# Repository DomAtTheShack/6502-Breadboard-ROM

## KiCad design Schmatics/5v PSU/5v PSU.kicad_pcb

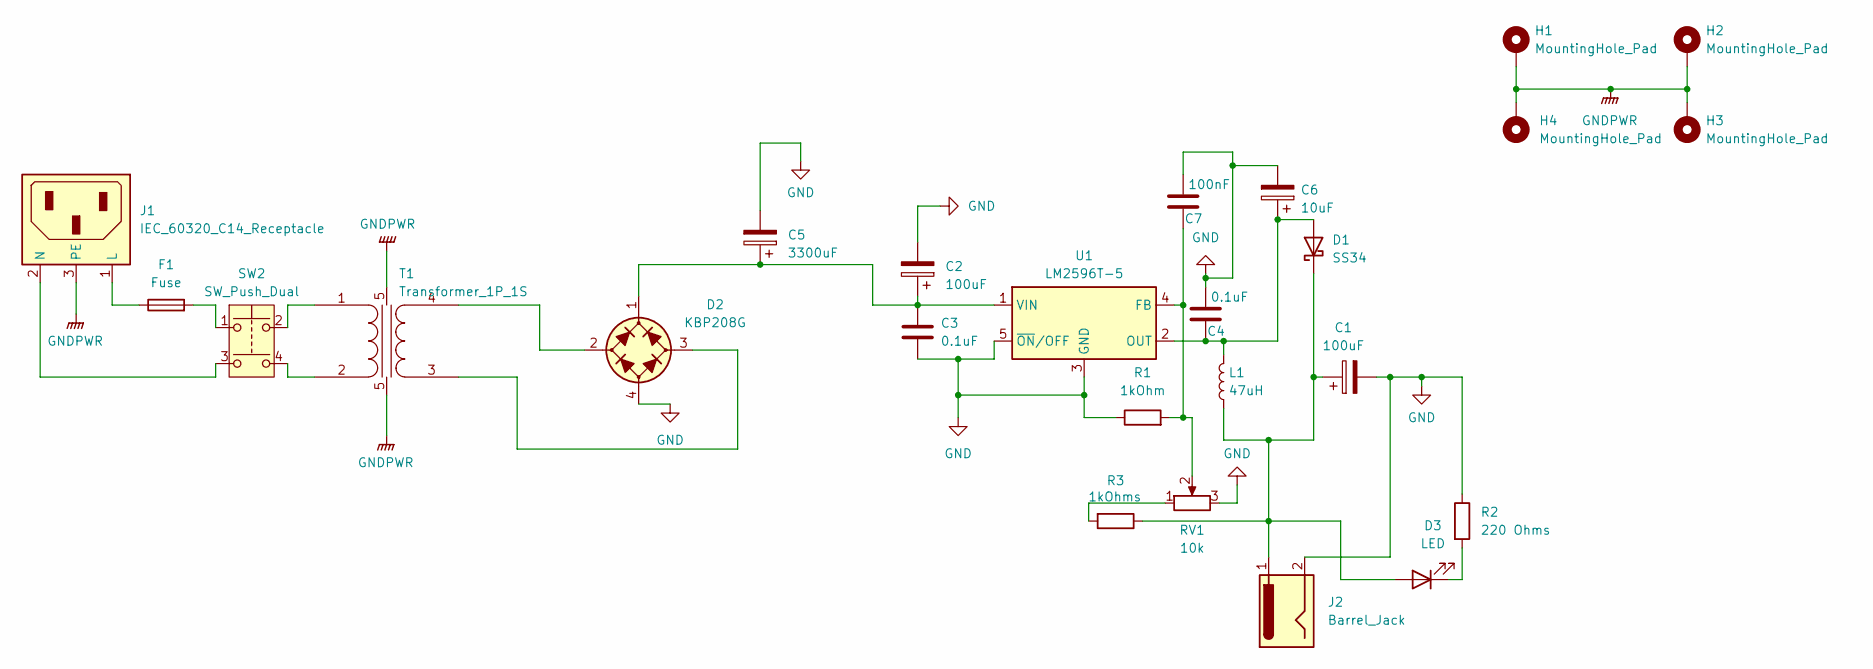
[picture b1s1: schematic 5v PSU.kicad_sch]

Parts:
C1, C2: 100uF; CP_Radial_D5.0mm_P2.00mm
C3, C4: 0.1uF; C_Axial_L3.8mm_D2.6mm_P7.50mm_Horizontal
C5: 3300uF; CP_Radial_D16.0mm_P7.50mm
C6: 10uF; CP_Radial_D5.0mm_P2.00mm
C7: 100nF; C_Axial_L3.8mm_D2.6mm_P7.50mm_Horizontal
D1: SS34; D_5W_P10.16mm_Horizontal
D2: KBP208G; Diode_Bridge_KBP
D3: LED; LED_D2.0mm_W4.8mm_H2.5mm_FlatTop
F1: Fuse; Fuseholder_Clip-6.3x32mm_Littelfuse_102071_Inline_P34.70x7.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
H1, H2, H3, H4: MountingHole_Pad; MountingHole_2.2mm_M2_DIN965_Pad
J1: IEC_60320_C14_Receptacle; IEC_THT
J2: Barrel_Jack; BarrelJack_SwitchcraftConxall_RAPC10U_Horizontal
L1: 47uH; L_Axial_L5.3mm_D2.2mm_P10.16mm_Horizontal_Vishay_IM-1
R1: 1kOhm; R_Axial_DIN0207_L6.3mm_D2.5mm_P10.16mm_Horizontal
R2: 220 Ohms; R_Axial_DIN0207_L6.3mm_D2.5mm_P10.16mm_Horizontal
R3: 1kOhms; R_Axial_DIN0207_L6.3mm_D2.5mm_P10.16mm_Horizontal
RV1: 10k; Potentiometer_Alps_RK09L_Single_Vertical
SW2: SW_Push_Dual; ST24_SWITCH
T1: Transformer_1P_1S; Transformer_166J
U1: LM2596T-5; TO-220-5_P3.4x3.7mm_StaggerOdd_Lead3.8mm_Vertical

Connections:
GND: C1.2, C2.2, C3.2, C4.1, C5.2, C6.2, C7.1, D2.4 (-), J2.2, R1.1, R2.1, RV1.3, U1.3 (GND), U1.5 (~ON/OFF)
GNDPWR: H1.1, H2.1, H3.1, H4.1, J1.3 (PE), T1.5 (EGND)
unnamed: C4.2, C6.1, D1.2 (A), L1.2, U1.2 (OUT)
unnamed: C1.1, D1.1 (K), D3.2 (A), J2.1, L1.1, R3.1
unnamed: D2.2 (1), T1.4 (SB)
unnamed: D2.3 (2), T1.3 (SA)
unnamed: C2.1, C3.1, C5.1, D2.1 (+), U1.1 (VIN)
unnamed: D3.1 (K), R2.2
unnamed: F1.2, SW2.1
unnamed: F1.1, J1.1 (L)
unnamed: J1.2 (N), SW2.3
unnamed: R3.2, RV1.1
unnamed: SW2.2, T1.1 (AA)
unnamed: SW2.4, T1.2 (AB)
unnamed: C7.2, R1.2, RV1.2, U1.4 (FB)

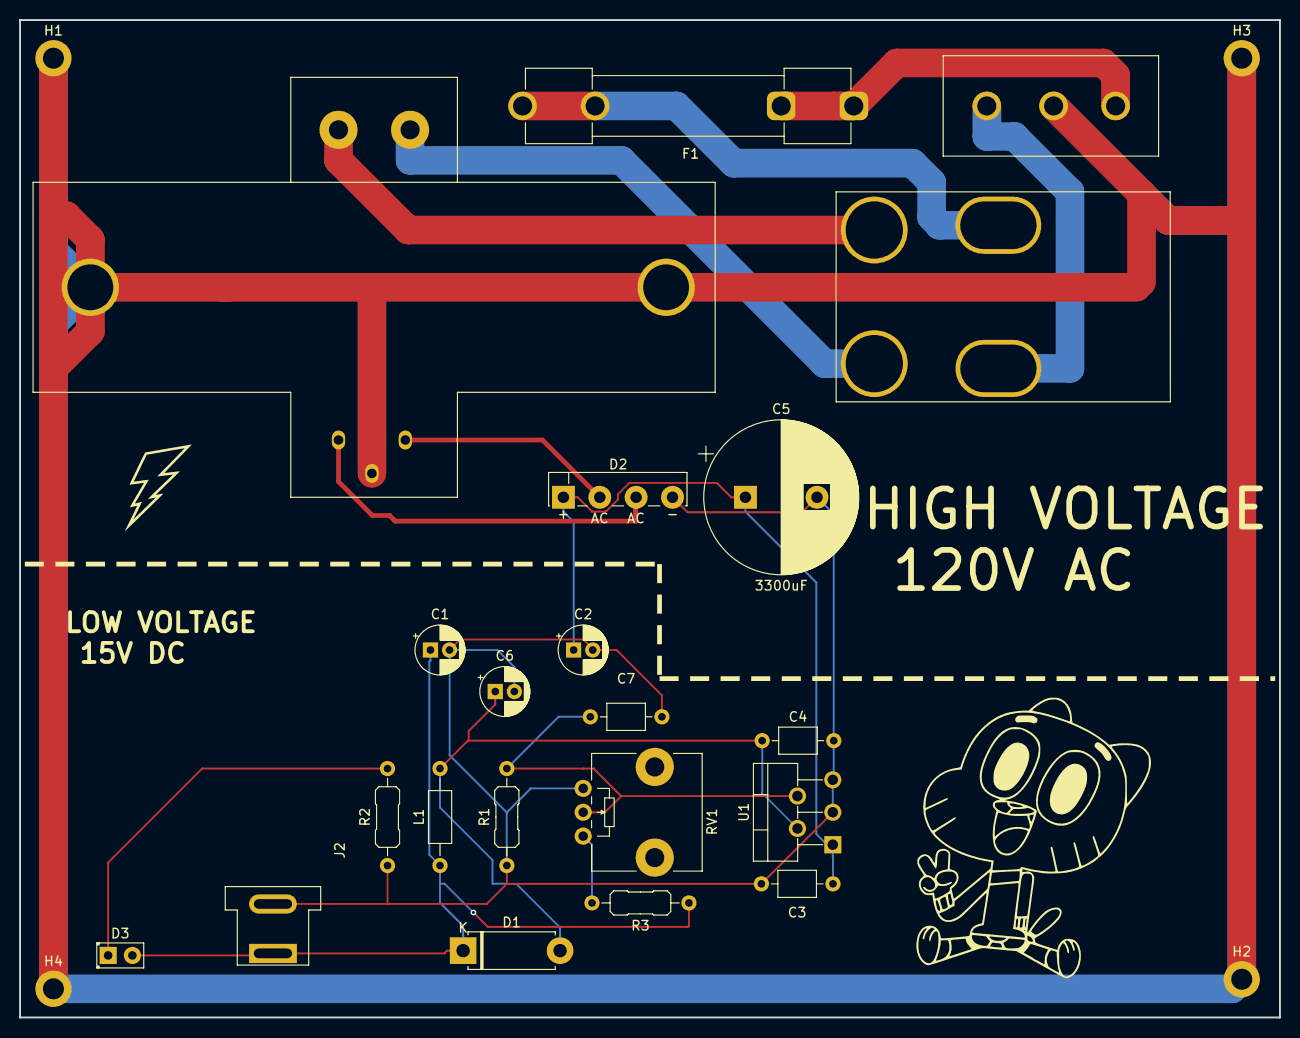
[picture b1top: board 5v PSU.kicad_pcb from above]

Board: 2 copper layers, 132.0 x 104.5 mm, 27 parts (0 on the bottom side), 15 nets.

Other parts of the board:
G1, G2: LOGO

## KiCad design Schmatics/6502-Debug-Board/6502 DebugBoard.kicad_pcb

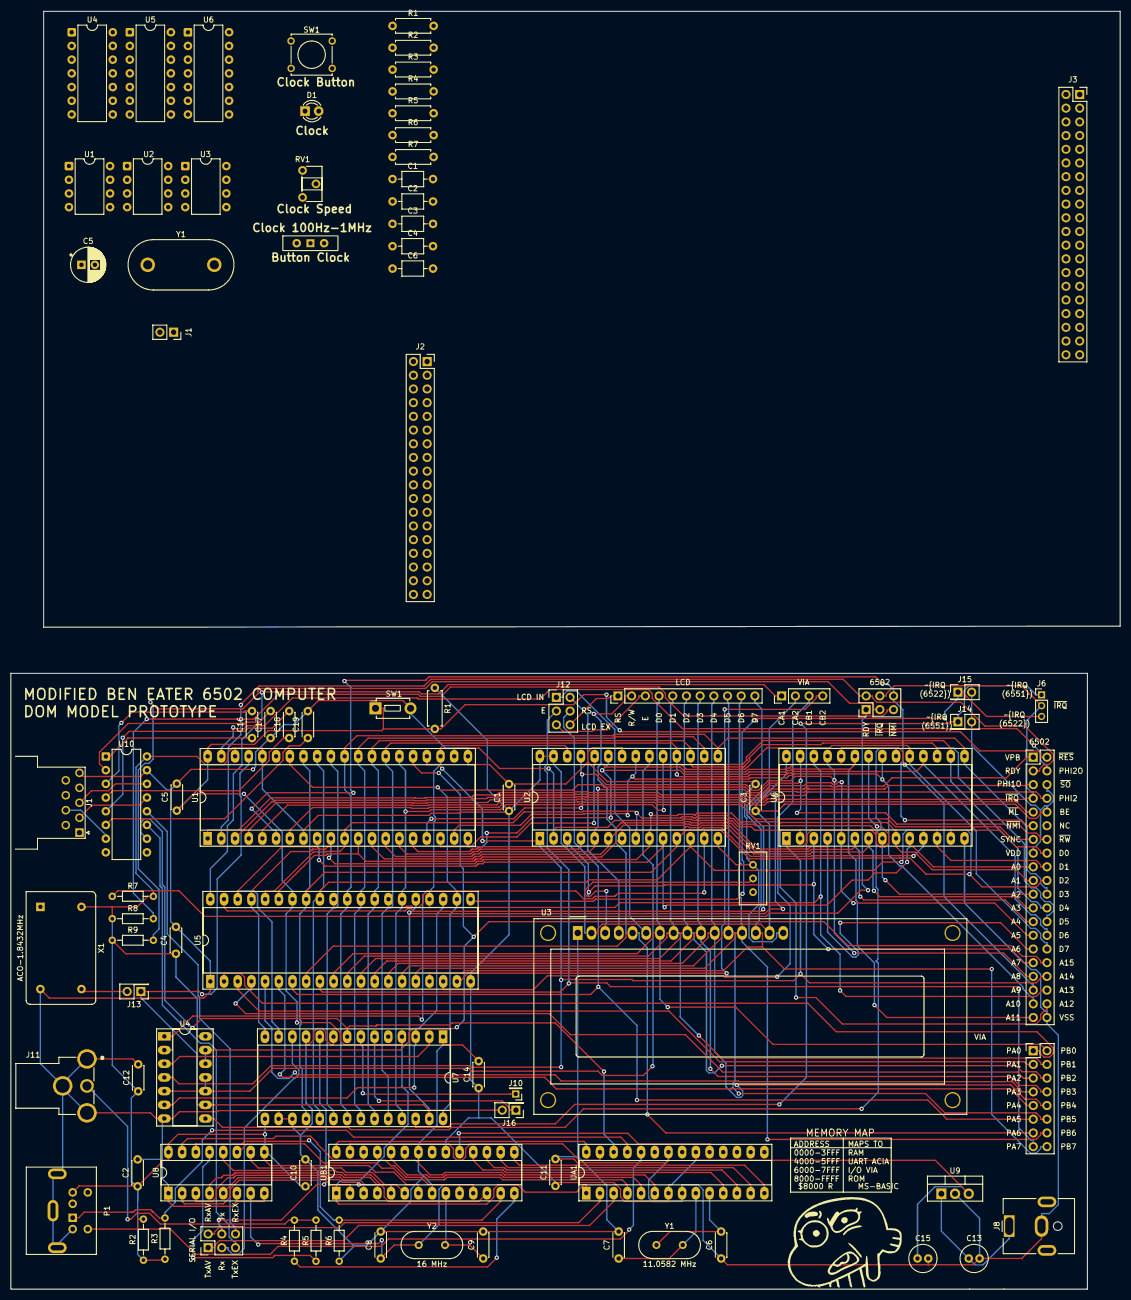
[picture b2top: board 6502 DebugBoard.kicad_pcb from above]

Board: 2 copper layers, 205.6 x 236.8 mm, 89 parts (0 on the bottom side), 141 nets.

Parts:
C1, C2#2, C3, C4, C10, C11, C12, C14: 0.1uF; C_Disc_D4.3mm_W1.9mm_P5.00mm
C1#2: 22pf; C_Axial_L3.8mm_D2.6mm_P7.50mm_Horizontal
C2: 100nf; C_Axial_L3.8mm_D2.6mm_P7.50mm_Horizontal
C3#2, C4#2, C6#2: 10nf; C_Axial_L3.8mm_D2.6mm_P7.50mm_Horizontal
C5: 47uf; CP_Radial_D6.3mm_P2.50mm
C5#2: 0.1; C_Disc_D4.3mm_W1.9mm_P5.00mm
C6, C7, C8, C9: 22pF; C_Disc_D4.3mm_W1.9mm_P5.00mm
C13, C15: 10uf; C_Radial_D5.0mm_H11.0mm_P2.00mm
C16, C17, C18, C19: 1uf; C_Disc_D4.3mm_W1.9mm_P5.00mm
D1: LED; LED_D3.0mm
J1: Conn_01x02; PinSocket_1x02_P2.54mm_Vertical
J1#2: DE9_Pins; DSUB-9_Socket_Horizontal_P2.77x2.54mm_EdgePinOffset9.40mm
J2: Conn_02x20_Odd_Even; PinHeader_2x20_P2.54mm_Vertical
J2#2: Conn_02x18_Top_Bottom; PinSocket_2x18_P2.54mm_Vertical
J3: Conn_01x04_Male; PinHeader_1x04_P2.54mm_Vertical
J3#2: Conn_02x20_Top_Bottom; PinSocket_2x20_P2.54mm_Vertical
J4, J7, J12: Conn_02x03_Odd_Even; PinHeader_2x03_P2.54mm_Vertical
J5: Conn_02x08_Odd_Even; PinHeader_2x08_P2.54mm_Vertical
J6: Conn_01x03; PinHeader_1x03_P2.00mm_Vertical
J8: Barrel_Jack; BarrelJack_CUI_PJ-063AH_Horizontal
J9: Conn_01x11_Male; PinHeader_1x11_P2.54mm_Vertical
J10: Conn_01x01; PinHeader_1x01_P2.00mm_Vertical
J11: RCJ-017; CUI_RCJ-017
J13, J14, J15, J16: Conn_02x01; PinHeader_2x01_P2.54mm_Vertical
P1: Mini-DIN_6pins; Connector_Mini-DIN_Female_6Pin_2rows
R1: 1K; R_Axial_DIN0207_L6.3mm_D2.5mm_P7.62mm_Horizontal
R1#2: 1M; R_Axial_DIN0207_L6.3mm_D2.5mm_P7.62mm_Horizontal
R2, R3, R6, R7#2, R8, R9: 10k; R_Axial_DIN0204_L3.6mm_D1.6mm_P7.62mm_Horizontal
R2#2, R5, R6#2, R7: 1k; R_Axial_DIN0207_L6.3mm_D2.5mm_P7.62mm_Horizontal
R3#2: 6.9k; R_Axial_DIN0207_L6.3mm_D2.5mm_P7.62mm_Horizontal
R4: 1k; R_Axial_DIN0204_L3.6mm_D1.6mm_P7.62mm_Horizontal
R4#2: 10k; R_Axial_DIN0207_L6.3mm_D2.5mm_P7.62mm_Horizontal
R5#2: 470 Ohms; R_Axial_DIN0204_L3.6mm_D1.6mm_P7.62mm_Horizontal
RV1: R_Potentiometer; Potentiometer_ACP_CA6-H2,5_Horizontal
RV1#2: R_POT_TRIM_US; Potentiometer_Bourns_3386C_Horizontal
SW1: SW_Push; SW_Tactile_Straight_KSA0Axx1LFTR
SW1#2: RESET; SW_PUSH_1P1T_6x3.5mm_H4.3_APEM_MJTP1243
SW2: SW_Nidec_CAS-120A1; SW_Slide-03_Wuerth-WS-SLTV_10x2.5x6.4_P2.54mm
U1: WD65C02; DIP-40_W15.24mm_Socket_LongPads
U1#2, U2, U3#2: LM555xN; DIP-8_W7.62mm
U2#2: 28C256; DIP-28_W15.24mm_Socket_LongPads
U3: WC1602A
U4: 74HC00; DIP-14_W7.62mm_Socket_LongPads
U4#2: 74LS04; DIP-14_W7.62mm
U5: 74LS08; DIP-14_W7.62mm
U5#2: WD65C22; DIP-40_W15.24mm_Socket_LongPads
U6: CY62256-70PC; DIP-28_W15.24mm_Socket_LongPads
U6#2: 74LS32; DIP-14_W7.62mm
U7: 6551; DIP-28_W15.24mm_Socket_LongPads
U8: 74HC166; DIP-16_W7.62mm_Socket_LongPads
U9: LM7805_TO220; TO-220-3_Vertical
U10: MAX232; DIP-16_W7.62mm
UA1: ATmega328P-PU; DIP-28_W7.62mm_Socket_LongPads
UB1: ATmega328P-PU; DIP-28_W7.62mm_Socket_LongPads
X1: ACO-1.8432MHz; Oscillator_DIP-14
Y1: 11.0582 MHz; Crystal_HC49-4H_Vertical
Y1#2: Crystal; Crystal_HC33-U_Vertical
Y2: 16 MHz; Crystal_HC49-4H_Vertical

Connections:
+5V: C1.1, C2#2.1, C3.1, C4.1, C10.1, C11.1, C12.1, C14.1, C15.1, J2.6, J2.10, J2.15, J2#2.1, J2#2.19, J14.2, J15.2, P1.4, R1.1, R2.1, R2#2.2, R3.1, R3#2.2, R4#2.2, R5.1, R7.1, R7#2.2, R8.1, R9.1, U1.8 (VCC), U1.36 (BE), U1.38 (~SO), U1#2.4 (R), U1#2.8 (VCC), U2.4 (R), U2.8 (VCC), U2#2.27 (~WE), U2#2.28 (VCC), U3.2 (VDD), U3.15 (LED(+)), U3#2.8 (VCC), U4.14 (VCC), U4#2.14 (VCC), U5.14 (VCC), U5#2.20 (VCC), U6.28 (VCC), U6#2.14 (VCC), U7.15 (VCC), U8.9 (~CLR), U8.16 (VCC), U9.3 (VO), U10.16 (VCC), UA1.7 (VCC), UA1.20 (AVCC), UB1.7 (VCC), UB1.20 (AVCC), X1.14 (Vcc)
GND: C1.2, C1#2.1, C2.1, C2#2.2, C3.2, C3#2.2, C4.2, C4#2.2, C5.2, C5#2.2, C6.1, C6#2.1, C7.2, C8.2, C9.2, C10.2, C11.2, C12.2, C13.2, C14.2, C15.2, C17.1, C19.2, J1#2.5, J2.40, J2#2.18, J2#2.36, J8.2, J11.1A, J11.1B, J11.1C, P1.3, P1.7 (Shell), R6.1, RV1#2.1, SW1.2, SW1#2.2, SW2.2 (B), U1.21 (GND), U1#2.1 (GND), U2.1 (GND), U2#2.14 (GND), U2#2.22 (~OE), U3.1 (VSS), U3.16 (LED(-)), U3#2.1 (GND), U3#2.6 (THR), U4.7 (GND), U4#2.7 (GND), U5.7 (GND), U5#2.1 (GND), U6.14 (GND), U6#2.7 (GND), U7.1 (GND), U7.9 (~CTS), U7.11 (~DTR), U7.16 (~DCD), U7.17 (~DSR), U8.1 (SER), U8.6 (CLK_INH), U8.8 (GND), U9.2 (GND), U10.15 (GND), UA1.8 (GND), UA1.22 (GND), UB1.8 (GND), UB1.22 (GND), X1.7 (GND)
unnamed: D1.2 (A), U6#2.3
unnamed: D1.1 (K), R7.2
unnamed: C1#2.2, J1.1, R1#2.2, Y1#2.2
unnamed: J1.2, R1#2.1, Y1#2.1
unnamed: J2.1, U1.1 (~VP)
unnamed: C5#2.1, J2.2, R1.2, SW1#2.1, U1.40 (~RESET), U5#2.34 (~RESET), U7.4 (~RESET), UA1.1 (~RESET/PC6), UB1.1 (~RESET/PC6)
unnamed: J2.3, J7.2, U1.2 (RDY)
unnamed: J2.4, U1.39 (PHI2out)
unnamed: J2.5, U1.3 (PHI1out)
unnamed: J2.7, J6.2, J7.4, U1.4 (~IRQ)
unnamed: J2.9, U1.5 (~ML)
unnamed: J2.11, J7.6, U1.6 (~NMI)
unnamed: J2.13, U1.7 (SYNC)
unnamed: J2.14, U1.34 (R/~W), U5#2.22 (R/~W), U6.27 (~WE), U7.28 (R/~W)
unnamed: J2.16, U1.33 (D0), U2#2.11 (D0), U5#2.33 (D0), U6.11 (Q0), U7.18 (D0)
unnamed: J2.17, U1.9 (A0), U2#2.10 (A0), U5#2.38 (RS0), U6.10 (A0), U7.13 (RS0)
unnamed: J2.18, U1.32 (D1), U2#2.12 (D1), U5#2.32 (D1), U6.12 (Q1), U7.19 (D1)
unnamed: J2.19, U1.10 (A1), U2#2.9 (A1), U5#2.37 (RS1), U6.9 (A1), U7.14 (RS1)
unnamed: J2.20, U1.31 (D2), U2#2.13 (D2), U5#2.31 (D2), U6.13 (Q2), U7.20 (D2)
unnamed: J2.21, U1.11 (A2), U2#2.8 (A2), U5#2.36 (RS2), U6.8 (A2)
unnamed: J2.22, U1.30 (D3), U2#2.15 (D3), U5#2.30 (D3), U6.15 (Q3), U7.21 (D3)
unnamed: J2.23, U1.12 (A3), U2#2.7 (A3), U5#2.35 (RS3), U6.7 (A3)
unnamed: J2.24, U1.29 (D4), U2#2.16 (D4), U5#2.29 (D4), U6.16 (Q4), U7.22 (D4)
unnamed: J2.25, U1.13 (A4), U2#2.6 (A4), U6.6 (A4)
unnamed: J2.26, U1.28 (D5), U2#2.17 (D5), U5#2.28 (D5), U6.17 (Q5), U7.23 (D5)
unnamed: J2.27, U1.14 (A5), U2#2.5 (A5), U6.5 (A5)
unnamed: J2.28, U1.27 (D6), U2#2.18 (D6), U5#2.27 (D6), U6.18 (Q6), U7.24 (D6)
unnamed: J2.29, U1.15 (A6), U2#2.4 (A6), U6.4 (A6)
unnamed: J2.30, U1.26 (D7), U2#2.19 (D7), U5#2.26 (D7), U6.19 (Q7), U7.25 (D7)
unnamed: J2.31, U1.16 (A7), U2#2.3 (A7), U6.3 (A7)
unnamed: J2.32, U1.25 (A15), U4.12, U4.13
unnamed: J2.33, U1.17 (A8), U2#2.25 (A8), U6.25 (A8)
unnamed: J2.34, U1.24 (A14), U2#2.1 (A14), U4.4, U6.1 (A14), U6.22 (~OE)
unnamed: J2.35, U1.18 (A9), U2#2.24 (A9), U6.24 (A9)
unnamed: J2.36, U1.23 (A13), U2#2.26 (A13), U4.1, U4.2, U5#2.24 (CS1), U6.26 (A13)
unnamed: J2.37, U1.19 (A10), U2#2.21 (A10), U6.21 (A10)
unnamed: J2.38, U1.22 (A12), U2#2.2 (A12), U6.2 (A12)
unnamed: J2.39, U1.20 (A11), U2#2.23 (A11), U6.23 (A11)
unnamed: J3.1, U5#2.40 (CA1)
unnamed: J3.2, U5#2.39 (CA2)
unnamed: J3.3, U5#2.18 (CB1)
unnamed: J3.4, U5#2.19 (CB2)
unnamed: J3#2.20, J3#2.40
unnamed: J4.1, UA1.3 (PD1)
unnamed: J4.2, UA1.2 (PD0)
unnamed: J4.3, U7.12 (Rx_Data)
unnamed: J4.4, U7.10 (Tx_Data)
unnamed: J4.5, U10.11 (T1IN)
unnamed: J4.6, U10.12 (R1OUT)
unnamed: J5.1, U5#2.2 (PA0)
unnamed: J5.2, J9.4, U3.7 (D0), U5#2.10 (PB0)
unnamed: J5.3, U5#2.3 (PA1)
unnamed: J5.4, J9.5, U3.8 (D1), U5#2.11 (PB1)
unnamed: J5.5, U5#2.4 (PA2)
unnamed: J5.6, J9.6, U3.9 (D2), U5#2.12 (PB2)
unnamed: J5.7, U5#2.5 (PA3)
unnamed: J5.8, J9.7, U3.10 (D3), U5#2.13 (PB3)
unnamed: J5.9, U5#2.6 (PA4)
unnamed: J5.10, J9.8, U3.11 (D4), U5#2.14 (PB4)
unnamed: J5.12, J9.9, U3.12 (D5), U5#2.15 (PB5)
unnamed: J5.13, J9.2, U3.5 (R/W), U5#2.8 (PA6)
unnamed: J5.14, J9.10, U3.13 (D6), U5#2.16 (PB6)
unnamed: J5.16, J9.11, U3.14 (D7), U5#2.17 (PB7)
unnamed: J7.1, R7#2.1
unnamed: J7.3, R9.2
unnamed: J7.5, R8.2
unnamed: J10.1, U7.7 (XLT0)
unnamed: J11.1 (V_In), R4.2, R5#2.2
unnamed: J12.1, U3.6 (E)
unnamed: J12.2, U3.4 (RS)
unnamed: J5.15, J12.3, U5#2.9 (PA7)
unnamed: J5.11, J12.4, U5#2.7 (PA5)
unnamed: J9.3, J12.5
unnamed: J9.1, J12.6
unnamed: J2.8, J13.1, J16.2, U1.37 (PHI2), U4.9, U5#2.25 (PHI2), U7.27 (PHI2)
unnamed: J13.2, X1.8 (OUT)
unnamed: J6.1, J14.1, U7.26 (~IRQ)
unnamed: J6.3, J15.1, U5#2.21 (~IRQ)
unnamed: J16.1, U7.6 (XTLI)
unnamed: R3#2.1, RV1.1
unnamed: R5.2, SW2.3 (A), U3#2.4 (R)
unnamed: R6#2.1, SW2.1 (C)
unnamed: C3#2.1, U1#2.5 (CV)
unnamed: R2#2.1, U1#2.7 (DIS)
unnamed: U1#2.3 (Q), U5.4
unnamed: C2.2, RV1.2, U1#2.2 (TR), U1#2.6 (THR)
unnamed: C4#2.1, U2.5 (CV)
unnamed: C5.1, U2.6 (THR), U2.7 (DIS)
unnamed: U2.3 (Q), U5.1
unnamed: R4#2.1, SW1.1, U2.2 (TR)
unnamed: U2#2.20 (~CS), U4.5, U4.10, U4.11
unnamed: C6#2.2, U3#2.5 (CV)
unnamed: U3#2.3 (Q), U4#2.1, U5.5
unnamed: R6#2.2, U3#2.2 (TR)
unnamed: RV1#2.2, U3.3 (VO)
unnamed: U4#2.2, U5.2
unnamed: U5.3, U6#2.1
unnamed: U5.6, U6#2.2
unnamed: U4.6, U5#2.23 (~CS2), U7.3 (~CS1)
unnamed: U4.8, U6.20 (~CS)
unnamed: U4.3, U7.2 (CS0)
unnamed: U8.2 (A), UB1.2 (PD0)
unnamed: U8.3 (B), UB1.3 (PD1)
unnamed: U8.4 (C), UB1.4 (PD2)
unnamed: C8.1, U8.7 (CLK), UB1.10 (XTAL2/PB7), Y2.1
unnamed: U8.5 (D), UB1.5 (PD3)
unnamed: U8.10 (E), UB1.6 (PD4)
unnamed: U8.11 (F), UB1.11 (PD5)
unnamed: U8.12 (G), UB1.12 (PD6)
unnamed: R6.2, U8.14 (H), UB1.13 (PD7)
unnamed: R5#2.1, U8.13 (QH)
unnamed: U8.15 (SH/~LD), UB1.26 (PC3)
unnamed: C13.1, J8.1, U9.1 (VI)
unnamed: C16.1, U10.1 (C1+)
unnamed: C16.2, U10.3 (C1-)
unnamed: C18.1, U10.4 (C2+)
unnamed: C18.2, U10.5 (C2-)
unnamed: J1#2.2, U10.13 (R1IN)
unnamed: J1#2.3, U10.14 (T1OUT)
unnamed: U7.8 (~RTS), U10.10 (T2IN), UA1.26 (PC3)
unnamed: J1#2.7, U10.7 (T2OUT)
unnamed: C17.2, U10.2 (VS+)
unnamed: C19.1, U10.6 (VS-)
unnamed: UA1.14 (PB0), UB1.15 (PB1)
unnamed: UA1.19 (PB5), UB1.19 (PB5)
unnamed: P1.5, R2.2, UA1.24 (PC1)
unnamed: P1.1, R3.2, UA1.25 (PC2)
unnamed: UA1.27 (PC4), UB1.27 (PC4)
unnamed: UA1.28 (PC5), UB1.28 (PC5)
unnamed: UA1.4 (PD2), UB1.25 (PC2)
unnamed: UA1.5 (PD3), UB1.24 (PC1)
unnamed: UA1.6 (PD4), UB1.23 (PC0)
unnamed: UA1.11 (PD5), UB1.18 (PB4)
unnamed: UA1.12 (PD6), UB1.17 (PB3)
unnamed: UA1.13 (PD7), UB1.16 (PB2)
unnamed: C7.1, UA1.9 (XTAL1/PB6), Y1.2
unnamed: C6.2, UA1.10 (XTAL2/PB7), Y1.1
unnamed: R4.1, UB1.14 (PB0)
unnamed: C9.1, UB1.9 (XTAL1/PB6), Y2.2

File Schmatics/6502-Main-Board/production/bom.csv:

Designator,Footprint,Quantity,Value,LCSC Part #
"C1, C10, C11, C12, C14, C2, C3, C4",C_Disc_D4.3mm_W1.9mm_P5.00mm,8,0.1uF,
C15,CP_Radial_D5.0mm_P2.00mm,1,10uF,
C5,C_Disc_D4.3mm_W1.9mm_P5.00mm,1,0.1,
"C6, C7, C8, C9",C_Disc_D4.3mm_W1.9mm_P5.00mm,4,22pF,
J10,PinHeader_2x01_P2.54mm_Vertical,1,Conn_02x01,
J11,CUI_RCJ-017,1,RCJ-017,
"J12, J4, J7",PinHeader_2x03_P2.54mm_Vertical,3,Conn_02x03_Odd_Even,
J2,PinHeader_2x20_P2.54mm_Vertical,1,Conn_02x20_Odd_Even,
J3,PinHeader_1x04_P2.54mm_Vertical,1,Conn_01x04_Male,
J5,PinHeader_2x08_P2.54mm_Vertical,1,Conn_02x08_Odd_Even,
J6,PinHeader_1x06_P2.54mm_Horizontal,1,Conn_01x06_Male,
J8,BarrelJack_CUI_PJ-063AH_Horizontal,1,Barrel_Jack,
J9,PinHeader_1x11_P2.54mm_Vertical,1,Conn_01x11_Male,
P1,Connector_Mini-DIN_Female_6Pin_2rows,1,Mini-DIN_6pins,
R1,R_Axial_DIN0207_L6.3mm_D2.5mm_P7.62mm_Horizontal,1,1K,
"R2, R3, R6",R_Axial_DIN0204_L3.6mm_D1.6mm_P7.62mm_Horizontal,3,10k,
R4,R_Axial_DIN0204_L3.6mm_D1.6mm_P7.62mm_Horizontal,1,1k,
R5,R_Axial_DIN0204_L3.6mm_D1.6mm_P7.62mm_Horizontal,1,470 Ohms,
RV1,Potentiometer_Bourns_3386C_Horizontal,1,R_POT_TRIM_US,
SW1,SW_PUSH_6mm_H5mm,1,RESET,
U1,DIP-40_W15.24mm_Socket_LongPads,1,WD65C02,
U2,DIP-28_W15.24mm_Socket_LongPads,1,28C256,
U3,WC1602A,1,WC1602A,
U4,DIP-14_W7.62mm_Socket_LongPads,1,74HC00,
U5,DIP-40_W15.24mm_Socket_LongPads,1,WD65C22,
U6,DIP-28_W15.24mm_Socket_LongPads,1,CY62256-70PC,
U7,DIP-28_W15.24mm_Socket_LongPads,1,6551,
U8,DIP-16_W7.62mm_Socket_LongPads,1,74HC166,
"UA1, UB1",DIP-28_W7.62mm_Socket_LongPads,2,ATmega328P-PU,
X1,Oscillator_DIP-14,1,ACO-1.8432MHz,
Y1,Crystal_HC49-4H_Vertical,1,11.0582 MHz,
Y2,Crystal_HC49-4H_Vertical,1,16 MHz,

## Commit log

2024-03-04 Add initial project structure and build files
    This commit introduces the initial structure for a 6502 project, including the creation of specific .idea configuration files, Makefile, main.s, bios.cfg, and the .gitignore. Each file was set with a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
2024-03-04 Update build configurations and refactor assembly code
    Removed the "Build & Run" configuration in favor of creating separate "Build Debug" and "Build Release" configurations. The Makefile has also been updated accordingly, with changes to building and cl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
2024-03-04 Adjust default Makefile goal and refine build process
    The Makefile has been updated to adjust the default goal to "rom.bin". Build and clean processes are refined by removing unnecessary routines and ensuring file name consistency in the build process. 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
2024-03-06 Added datasheet pdfs and updated main.s
2024-03-09 Refactor low-level display code and implement new functionality
    This revision refactors low-level display control instructions and introduces new 'flickEnable' and 'writeChar' subroutines to improve code readability and efficiency. The 'writeChar' subroutine has 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
2024-03-21 Update schematic configuration and add new components
    The schematic configuration was updated to include presets and detailed design settings. Two new elements, a trim-potentiometer and an LCD display, were also added to the PSI schematic. In addition, 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
2024-03-27 Schemat
2024-04-05 Add new power symbols, a resistor and a NPN transistor to KiCad schematic
    In this commit, new "+5V", "Earth" power symbols and a "NPN" transistor were added into the "6502Computer.kicad_sch" KiCad schematic for realistic power simulation. A 10k resistor ("R9") has also bee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
2024-04-10 Add switch to schematic and update makefile
    This commit introduces a Single Pole Single Throw (SPST) switch to Kicad schematic and adjust wire connections accordingly. The Makefile is also updated to include 'WriteChip' command for writing bin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
2024-04-12 Add interrupt registers and delay routine in assembly language
    Enhancements made in the assembly language program include addition of interrupt registers and initiation of a delay routine. These modifications are constructed for better handling of interrupts and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
2025-04-30 PCB Updated
2025-05-11 Scripts and Stuff
2025-05-18 MAJOR push with big basic improvements
2025-05-19 Custom Commnads
2025-05-19 Added OK flag
2025-06-18 Schumatic Sound Chip
2025-06-18 Move stuff around + 5v PSU
